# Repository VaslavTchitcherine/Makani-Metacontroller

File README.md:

Makani Metacontoller
"Quis custodiet ipsos custodes?"

We bought Makani's wind kite dyno rig at their going-out-of-business auction, including 16 Yasa/Makani axial flux motors and contollers.

Makani open-sourced all their software, including motor firmware and control software:
	https://github.com/google/makani

The Makani avionics I/O network is described here:
	https://storage.googleapis.com/x-prod.appspot.com/files/Makani_TheEnergyKiteReport_Part2.pdf
(I'd tell a joke here about UDP, but not everyone would get it.)

And I posted a motor controller teardown:
	https://endless-sphere.com/forums/viewtopic.php?f=30&t=108154

Yes, the gigantic pile of Makani code does build and run, but I wanted a standalone way of controlling speed setpoint on simple and cheap hardware, to be able to reuse the motors in various vehicle applications. 

This git contains a small subset of the Makani build, containing only the code needed by the motor_client.py script.  Most of this is code from the Makani git repository.  The subdir lib contains .so dynamic libraries needed by the python code, ELF x86-64 format.  (Scripts for building these libraries were generated by by parsing the verbose output of the massive bazel build, then the scripts were executed to build the libraries.  These build scripts are in the debazel/buildcmds subdir.)

Instead of trying to port motor_client.py to ARMv7, I instrumented low-level _SendInternal() in aio.py to dump the hex being sent out (as mulitcast UDP) on the AIO network.  This output can then be replayed using the trivial script replay.py, which runs successfully on a Pi, without requiring any additional libraries or python packages.
It also works on any architecture (with the correct endian-ness).
The Runner() thread in motor_client.py broadcasts the desired state messages at 100 Hz.
Here's how to replay the commands captured from a run of motor_client.py:
	replay.py < replays/spinup

Here is a video of the motor spinning, with a Pruis hall effect accelerator
pedal connected to the A/D converter on the Pi 3B running the throttle.py script:
	http://rp.to/z1ohz
The throttle.py script simply stuffs omega setpoints into the final 175 char line that is being replayed,
to dynamically control the motor speed:
	throttle.py --init=replays/init

The metacontroller box in the video also contains a 12 to 60 VDC boost converter to power the Makani controller and a Fiberfin POF to ethernet media converter (https://fiberfin.com/product/ff-mce300t-229).
Design files for the simple A/D converter Pi hat are in the adc subdir.

Note that the replay.py and throttle.py scripts assume we are talking to the motor called PTI by Makani, which is at 192.168.1.16.  Using the "program" executable from the full Makani bazel build you can run:
	program motor_pti
to program your motor at 192.168.1.16 with the settings in network.yaml.

Many thanks to ex-Makani engineer Johnny Sun <jsun9679@gmail.com> who provided many clues that helped me understand how to get these motors spinning.

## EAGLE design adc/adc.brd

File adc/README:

Eagle PCB design files for single channel 16 bit a/d coverter Raspberry Pi hat.
Used to read analog signal from Prius accelerator pedal in script throttle.py

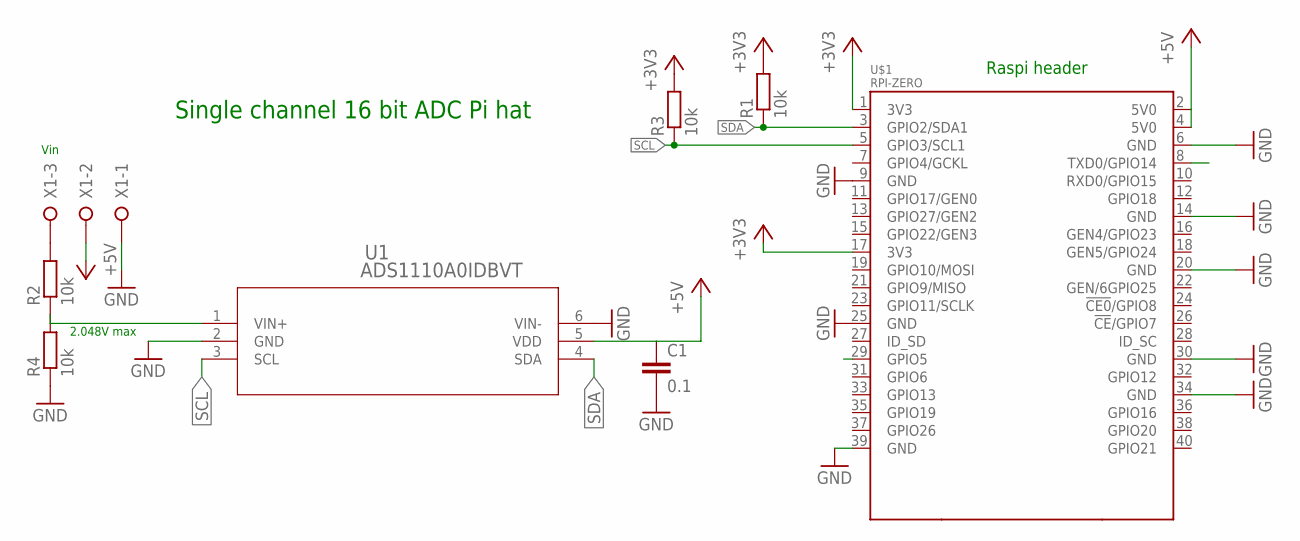
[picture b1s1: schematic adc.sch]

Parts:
C1: 0.1; C0603
R1, R2, R3, R4: 10k; R0603
U1: ADS1110A0IDBVT; DBV6
U$1: RPI-ZERO; RASPBERRYPI_BASTELSTUBE_V13_RASPI_BOARD_B+_FULL
X1: W237-3E

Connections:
3V3@2: U$1.17 (3V3)
+3V3: R1.2, R3.2, U$1.1 (3V3)
+5V: C1.1, U1.5 (VDD), U$1.2 (5V0), U$1.4 (5V0), X1.2
GND: C1.2, R4.1, U1.2 (GND), U1.6 (VIN-), U$1.6 (GND), U$1.9 (GND), U$1.14 (GND), U$1.20 (GND), U$1.25 (GND), U$1.30 (GND), U$1.34 (GND), U$1.39 (GND), X1.1
unnamed: R2.1, R4.2, U1.1 (VIN+)
unnamed: R2.2, X1.3
PGATE: U$1.29 (GPIO5)
SCL: R3.1, U1.3 (SCL), U$1.5 (GPIO3/SCL1)
SDA: R1.1, U1.4 (SDA), U$1.3 (GPIO2/SDA1)
TX: U$1.8 (TXD0/GPIO14)

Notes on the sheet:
Raspi header
2.048V max
Vin
Single channel 16 bit ADC Pi hat

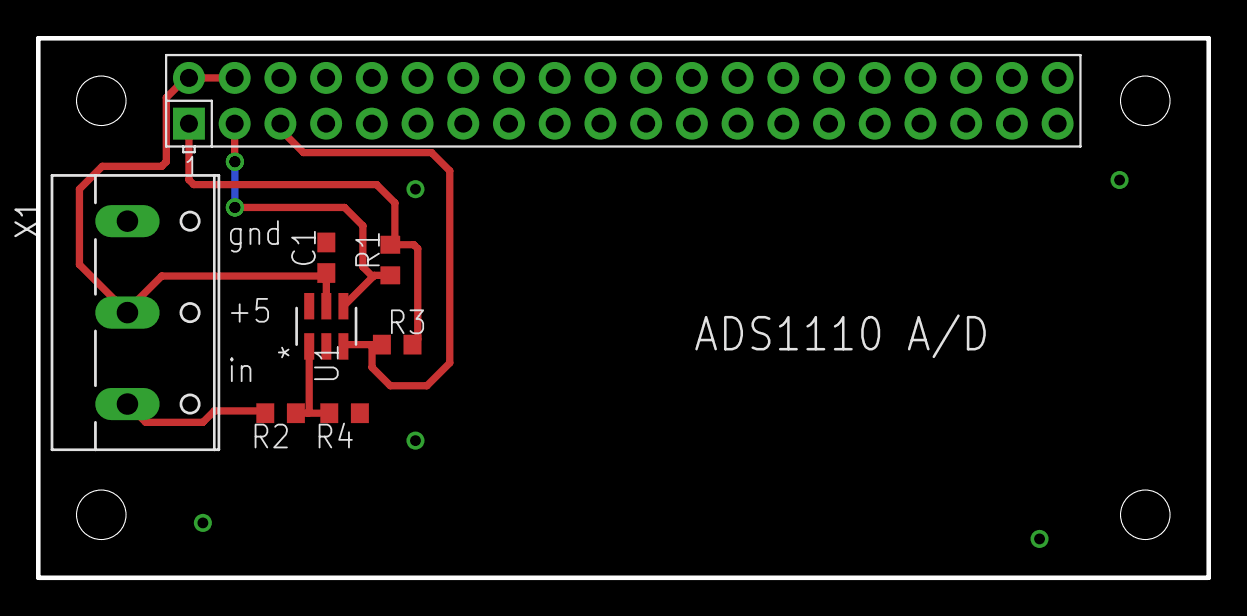
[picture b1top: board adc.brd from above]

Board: 2 copper layers, 65.0 x 30.0 mm, 8 parts (0 on the bottom side), 7 nets.
